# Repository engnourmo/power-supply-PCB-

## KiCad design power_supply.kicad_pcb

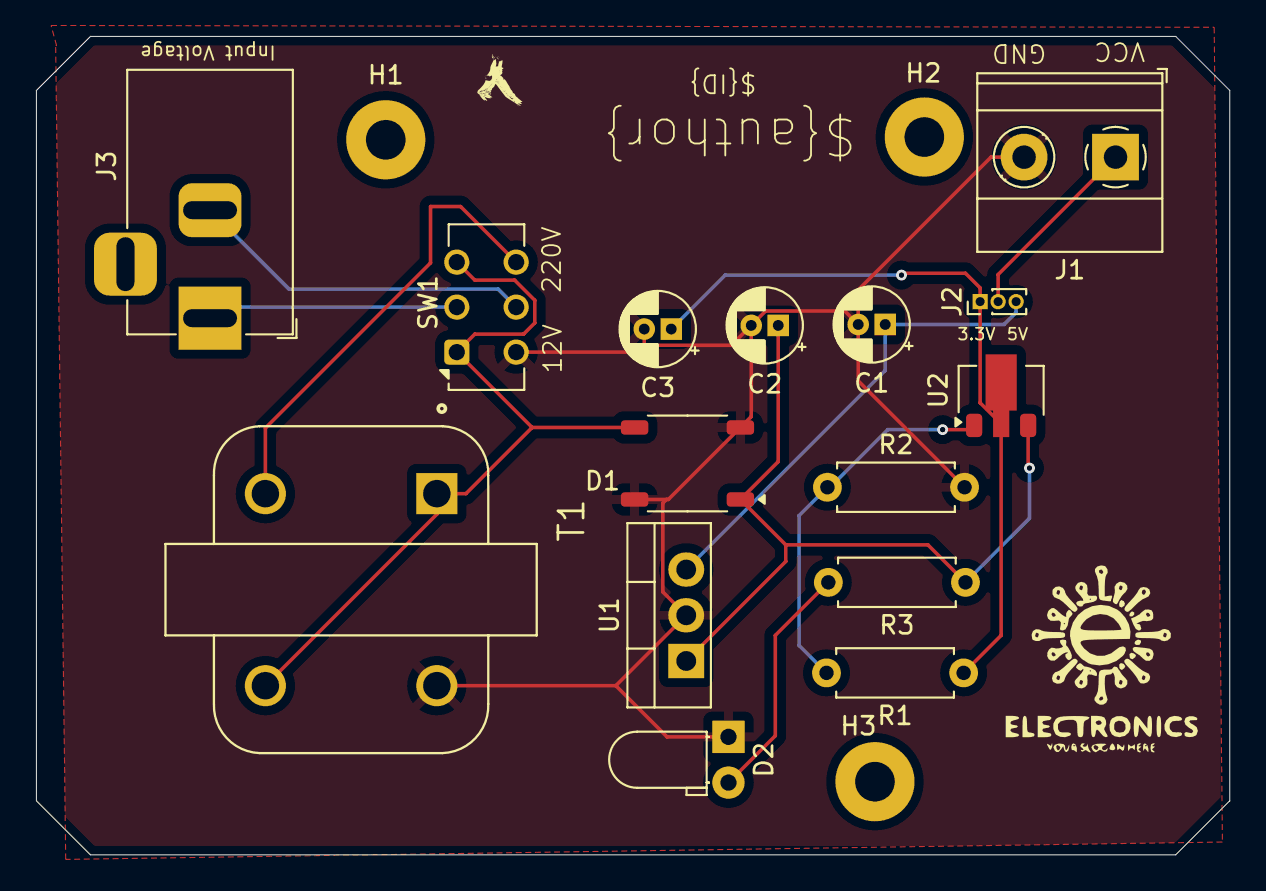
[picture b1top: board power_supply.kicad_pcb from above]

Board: 2 copper layers, 66.3 x 45.5 mm, 18 parts (0 on the bottom side), 11 nets.

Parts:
C1, C2, C3: C_Polarized; CP_Radial_D4.0mm_P1.50mm
D1: MDB10S; TSSOP-4_4.4x5mm_P4mm
D2: LED; LED_D3.0mm_Horizontal_O1.27mm_Z2.0mm
H1, H2, H3: MountingHole; MountingHole_2.2mm_M2_Pad
J1: Screw_Terminal_01x02; TerminalBlock_Phoenix_MKDS-1,5-2-5.08_1x02_P5.08mm_Horizont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
J2: Conn_01x03_Pin; PinHeader_1x03_P1.00mm_Vertical
J3: Jack-DC; BarrelJack_Horizontal
R1, R2, R3: R; R_Axial_DIN0207_L6.3mm_D2.5mm_P7.62mm_Horizontal
SW1: SW_Push_DPDT; SW_CK_JS202011CQN_DPDT_Straight
T1: TY-311P; XFMR_TY-311P
U1: LM7805_TO220; TO-220-3_Vertical
U2: LM317L_SOT-89; SOT-89-3

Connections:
/3.3V: C3.1, J2.1, R1.1, U2.2 (VO)
/5V: C1.1, J2.3, U1.3 (VO)
/VCC: C2.1, D1.1 (+), R3.1, U1.1 (VI), U2.3 (VI)
GND: C1.2, C2.2, C3.2, D1.2 (-), D1.4, D2.1 (K), J1.2, R2.2, SW1.6 (C), T1.6, U1.2 (GND)
unnamed: D1.3, SW1.1 (A), SW1.3 (C), T1.1, T1.4
unnamed: D2.2 (A), R3.2
unnamed: J1.1, J2.2
unnamed: J3.1, SW1.2 (B)
unnamed: J3.2, SW1.5 (B)
unnamed: SW1.4 (A), T1.3
unnamed: R1.2, R2.1, U2.1 (ADJ)

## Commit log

2025-03-15 added the project files
2025-03-15 added gerber files
2025-03-15 modified some tracks
2025-03-16 added schematic as a PDF
